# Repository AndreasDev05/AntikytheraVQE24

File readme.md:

# Einleitung

Eine eigene Uhr zu bauen war ein Vorhaben das ich seit 35 Jahre habe. Damals bekam ich Anzeigen (VQE24) und einen entsprechenden Mikrocontroller geschenkt. Dieser war 2. Wahl und funktionierte auch nicht richtig. Ich bin nie über einen fliegenden Aufbau hinaus gekommen. Das möchte ich jetzt ändern und die Welt auch noch damit "bereichern". Bitte habe Geduld, vieles was ich hier tue, mache zum ersten Mal :wink: .

# Projektstatus:
**Software**

:construction: :construction_worker:

**Hardware (PCB)**

Die Entwicklung der Leiterplatte ist erst einmal fertig, ich habe die "Produktion" beauftragt :relaxed:.

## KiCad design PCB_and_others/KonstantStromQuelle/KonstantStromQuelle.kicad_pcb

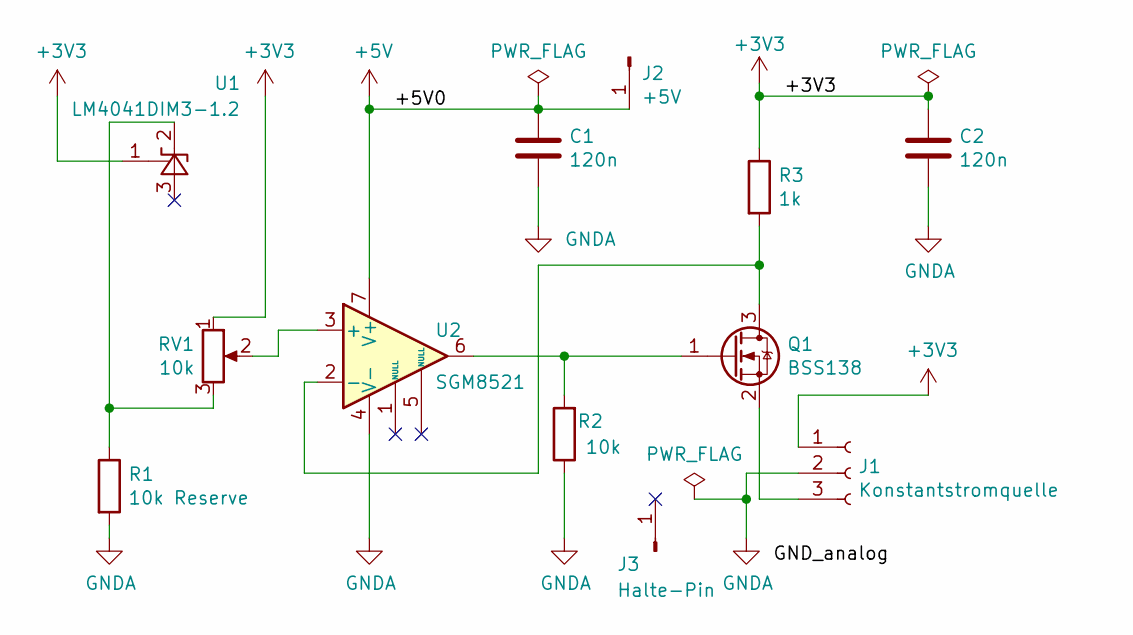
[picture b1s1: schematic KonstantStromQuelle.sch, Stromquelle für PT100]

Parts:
C1, C2: 120n; C_0805_2012Metric_Pad1.15x1.40mm_HandSolder
J1: Konstantstromquelle; TO-92L_Inline_Wide
J2: +5V; Pin_D0.9mm_L10.0mm_W2.4mm_FlatFork
J3: Halte-Pin; Pin_D0.9mm_L10.0mm_W2.4mm_FlatFork
Q1: BSS138; SOT-23
R1: 10k Reserve; R_1206_3216Metric_Pad1.42x1.75mm_HandSolder
R2: 10k; R_1206_3216Metric_Pad1.42x1.75mm_HandSolder
R3: 1k; R_1206_3216Metric_Pad1.42x1.75mm_HandSolder
RV1: 10k; Potentiometer_Bourns_3296W_Vertical
U1: LM4041DIM3-1.2; SOT-23
U2: SGM8521; SO-8_3.9x4.9mm_P1.27mm

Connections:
+3V3: C2.1, J1.1, R3.1, RV1.1, U1.1 (FB)
+5V: C1.1, J2.1, U2.7 (V+)
GNDA: C1.2, C2.2, J1.2, R1.2, R2.1, U2.4 (V-)
unnamed: J1.3, Q1.2 (S)
unnamed: Q1.1 (G), R2.2, U2.6
unnamed: Q1.3 (D), R3.2, U2.2 (-)
unnamed: R1.1, RV1.3, U1.2 (K)
unnamed: RV1.2, U2.3 (+)

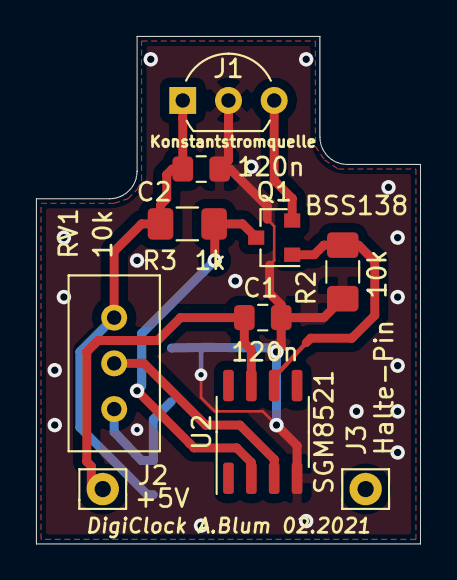
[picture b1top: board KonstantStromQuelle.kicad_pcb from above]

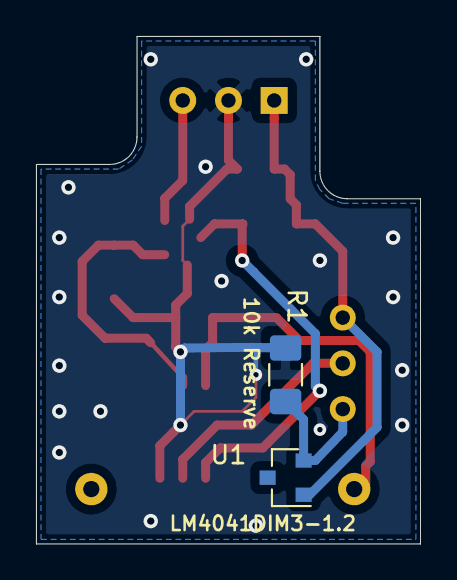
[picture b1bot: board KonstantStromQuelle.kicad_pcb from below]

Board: 2 copper layers, 21.3 x 28.2 mm, 12 parts (2 on the bottom side), 8 nets.

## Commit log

2020-06-15 Upload other projectfiles
2020-06-15 Test upload
2020-06-15 Erste Projektbemerkunk
2020-06-15 Erste Projektbemerkung
2020-06-15 Changes for testing
    Changes for testing
2020-06-15 3V3 V_regulator insert
2020-06-15 dir Debug ignore
2020-06-15 Wrong copy
2020-06-15 Wrong copy too
2020-06-17 Edit readme
2020-06-17 Fehlerkorrektur
2020-06-17 Error2
2020-06-17 Error 3
    Syncfehler
2020-06-22 Replace INTs and first impl. ADC_scheduler
2020-06-22 kl. Korr.
2020-06-23 Change int
2020-06-23 Next impl. ADC_scheduler
2020-06-27 first test ADC_scheduler
2020-06-27 first project-picture
2020-07-04 Implemetation of CPU-temperature output
2020-07-04 first connect of displayconnector
2020-07-04 Remove debug parts
2020-07-21 Work at connector pinlayout and groundmesh
2020-07-30 impl decimalpoint & button fkt.
2020-08-02 next short steps
2020-08-14 btn. basic functions
2020-08-17 btn impl. and first void ptr.
    Create separate files for the key functions and usage of void pointers.
2020-08-23 Impl. Btn and menue
2020-08-31 first Impl. alarm; err. corr.
2020-09-01 first program flow chart
2020-09-02 diagram bigger
2020-09-04 code cleaning
2020-09-05 Update pin layout to the front panel
2020-09-06 new design disp.-connector
2020-09-24 Imp. ADC-Log. and menuelog.
2020-09-24 rename file
2020-09-27 little changes
2020-10-04 circuit diagram almost finished
2020-10-05 small changes to the circuit diagram
    Power
    measurement of voltage
2020-10-06 Batt. meas.
2020-10-12 controlling ADC-power
2020-10-16 PCB Front ready (almost finished)
2020-10-28 Layout Mainboard
2020-11-03 Mainboard Layout
    Problem with Goundplane
2020-11-07 PCB is in produktion
2020-11-07 Dok. that the PCB is ready and in Produktion
2020-11-07 smiley
2020-11-09 smale changes
2020-11-12 PDF-docs and error-documentation
2020-11-23 error correction
    insert a description, what is wrong
2020-12-09 correction of the assignment
2020-12-10 first adapten
2021-01-11 Timing Ver1.0 ready
    calibration not perfect
    first test of KiCad
2021-01-11 small correction
2021-01-12 impl. Switch
2021-01-12 Conflict ods-file
2021-01-12 the conflict-file is newer
2021-02-14 Beeper Impl.
2021-04-04 Strart FlashWrite and PCB Ver.1.1 is ready
2021-09-14 Start the menu implementation
2021-12-10 Create LICENSE
